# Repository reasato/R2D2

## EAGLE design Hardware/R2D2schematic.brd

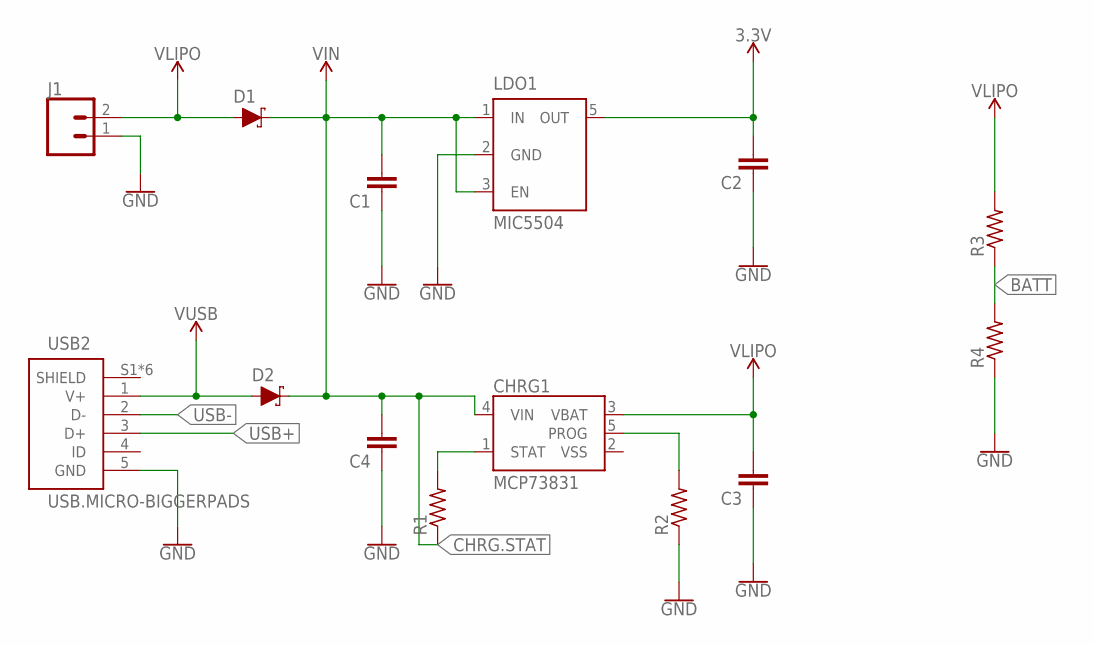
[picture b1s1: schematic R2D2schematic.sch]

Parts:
C1, C2, C3, C4: CAPACITOR0603; C0603
CHRG1: MCP73831; SOT23-5
D1, D2: SCHOTTKY-USC; USC
J1: CONN_02; 1X02
LDO1: MIC5504; SOT23-5
R1, R2, R3, R4: RESISTOR0603; R0603
USB2: USB.MICRO-BIGGERPADS; USB-MICRO-01.BIGGERPADS

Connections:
3.3V: C2.2, LDO1.5 (OUT)
BATT: R3.1, R4.2
CHRG.STAT: C1.2, C4.2, CHRG1.4 (VIN), D1.- (C), D2.- (C), LDO1.1 (IN), LDO1.3 (EN), R1.1
GND: C1.1, C2.1, C3.1, C4.1, J1.1, LDO1.2 (GND), R2.1, R4.1, USB2.5 (GND)
unnamed: CHRG1.1 (STAT), R1.2
unnamed: CHRG1.5 (PROG), R2.2
USB+: USB2.3 (D+)
USB-: USB2.2 (D-)
VLIPO: C3.2, CHRG1.3 (VBAT), D1.+ (A), J1.2, R3.2
VSS: CHRG1.2 (VSS)
V_USB: D2.+ (A), USB2.1 (V+)

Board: 2 copper layers, 14 parts (0 on the bottom side), 8 nets, no tracks yet.

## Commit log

2020-02-02 Lesson 2 work: hardware and firmware
